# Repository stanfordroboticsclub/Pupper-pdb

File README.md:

# Pupper Power Distribution Board for Teensy
This is a custom power distribution board for the versions of Pupper that generate PWM signals from Teensy's that have the smaller footprint. It also has a spot to attach a Sparkfun BNO080 IMU, connected to the Teensy over I2C. 

Don't know what Pupper is? It's a cheap dynamics quadruped robot that you can build at home.
- Check out the [Project Page](https://stanfordstudentrobotics.org/pupper)
- Check out the [Code](https://github.com/stanfordroboticsclub/stanfordquadruped)

## Fabrication
1. Upload Gerbers.zip (in this directory) to the quoting mechanism on jlcpcb.com
2. It'll then give you some options on how you want the pcb made
3. Make sure you specify 2oz copper to support the high current from the servos.
4. You can leave everything else as default!

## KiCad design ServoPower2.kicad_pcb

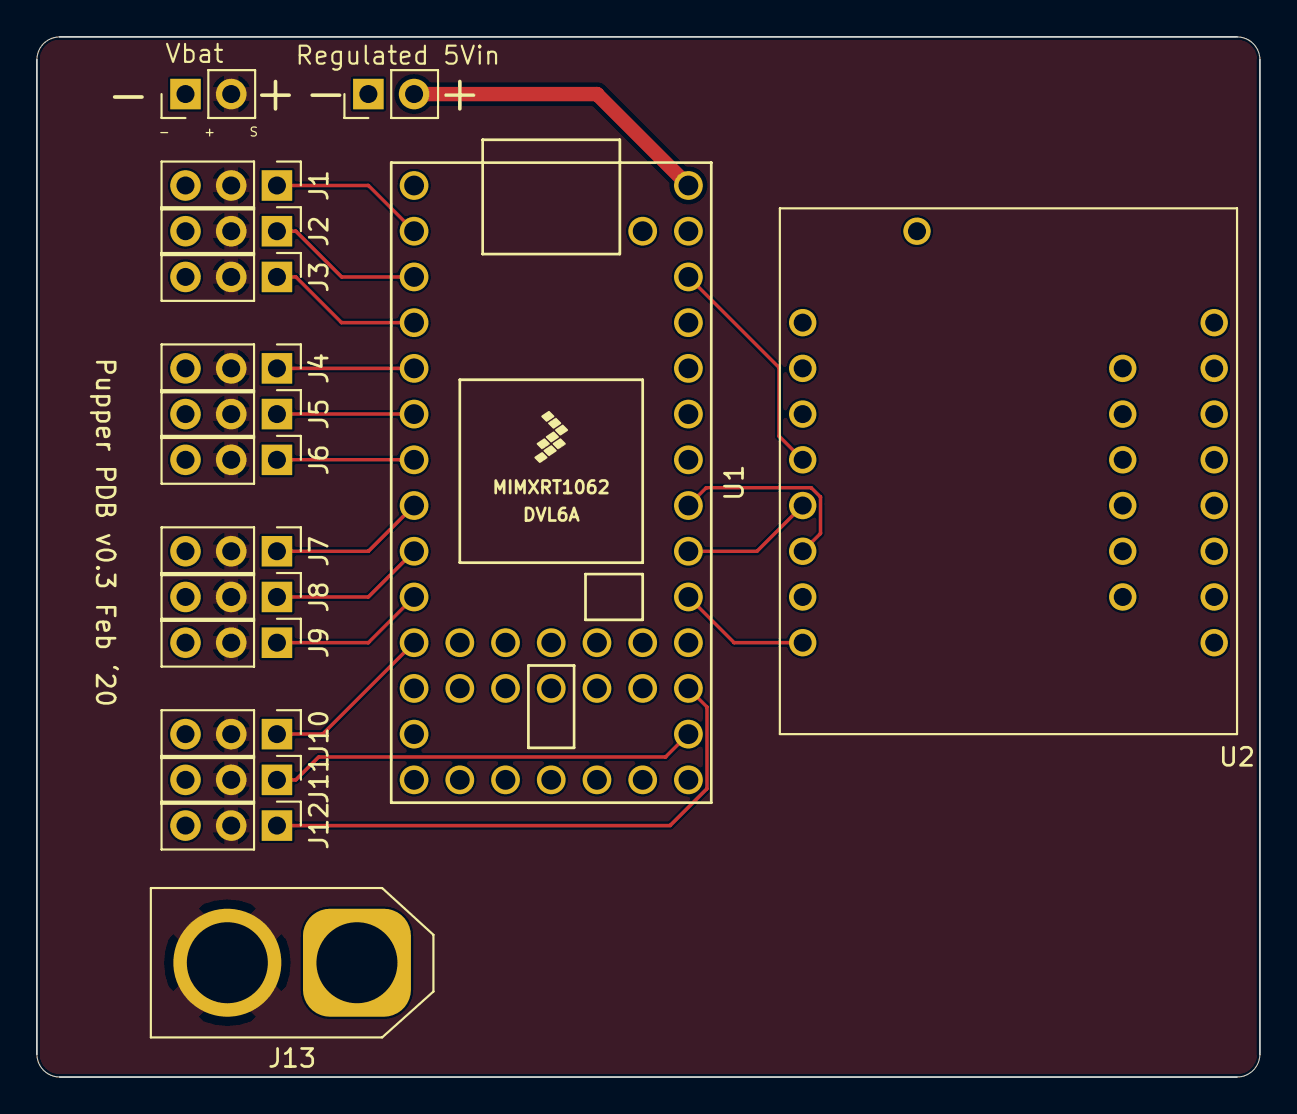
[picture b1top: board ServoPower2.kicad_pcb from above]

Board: 2 copper layers, 67.9 x 57.8 mm, 17 parts (0 on the bottom side), 18 nets.

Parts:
J1, J2, J3, J4, J5, J6, J7, J8, J9, J10, J11, J12: Conn_01x03; PinHeader_1x03_P2.54mm_Vertical
J13: Conn_01x02; AMASS_XT60-M_1x02_P7.20mm_Vertical
J14, J15: Conn_01x02; PinHeader_1x02_P2.54mm_Vertical
U1: Teensy4.0; Teensy40
U2: IMUBN

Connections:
+5V: J15.2, U1.33
/INT: U1.24, U2.8
/S11: J1.1, U1.2
/S12: J2.1, U1.3
/S13: J3.1, U1.4
/S21: J4.1, U1.5
/S22: J5.1, U1.6
/S23: J6.1, U1.7
/S31: J7.1, U1.8
/S32: J8.1, U1.9
/S33: J9.1, U1.10
/S41: J10.1, U1.11
/S42: J11.1, U1.21
/S43: J12.1, U1.22
/SCL: U1.26, U2.6
/SDA: U1.25, U2.5
GND: J1.3, J2.3, J3.3, J4.3, J5.3, J6.3, J7.3, J8.3, J9.3, J10.3, J11.3, J12.3, J13.1, J14.1, J15.1, U1.1, U1.17, U1.32, U2.3
VDD: J1.2, J2.2, J3.2, J4.2, J5.2, J6.2, J7.2, J8.2, J9.2, J10.2, J11.2, J12.2, J13.2, J14.2

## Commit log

2020-04-05 clean up
2020-04-18 updated to have IMU
2020-04-18 added 3v3
2020-04-19 Files for the IMU symbol
2020-04-19 added local dependency to imu symbol and footprint
